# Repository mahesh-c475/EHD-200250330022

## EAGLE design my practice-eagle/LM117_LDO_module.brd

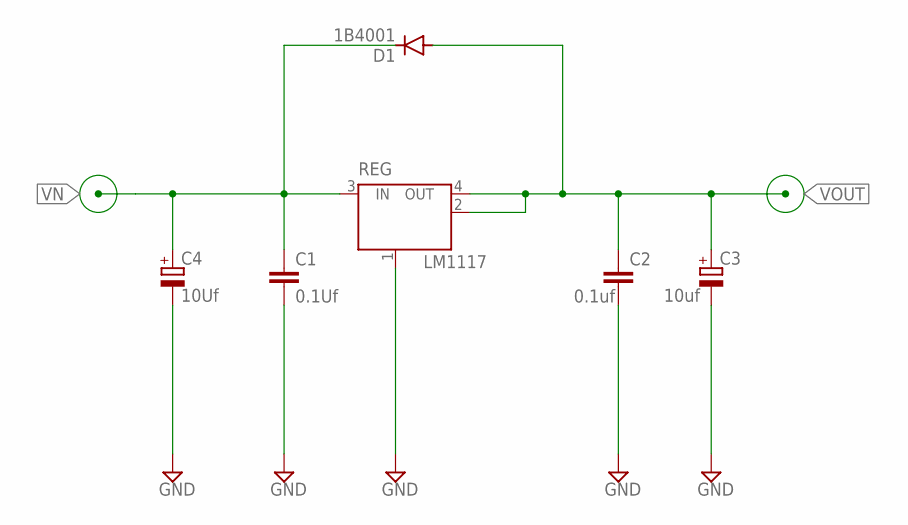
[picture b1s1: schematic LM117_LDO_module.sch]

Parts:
C1: 0.1Uf; C1206
C2: 0.1uf; C1206
C3: 10uf; CT3216
C4: 10Uf; CT3216
D1: 1B4001; DO-214AC
REG: LM1117; SOT223

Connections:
GND: C1.2, C2.2, C3.-, C4.-, REG.1 (GND/ADJ)
VN: C1.1, C4.+, D1.C, REG.3 (IN)
VOUT: C2.1, C3.+, D1.A, REG.2 (OUT), REG.4 (OUT)

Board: 2 copper layers, 6 parts (0 on the bottom side), 3 nets, no tracks yet.
